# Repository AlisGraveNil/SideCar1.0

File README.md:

# SideCar
 a macropad with nav and num clusters

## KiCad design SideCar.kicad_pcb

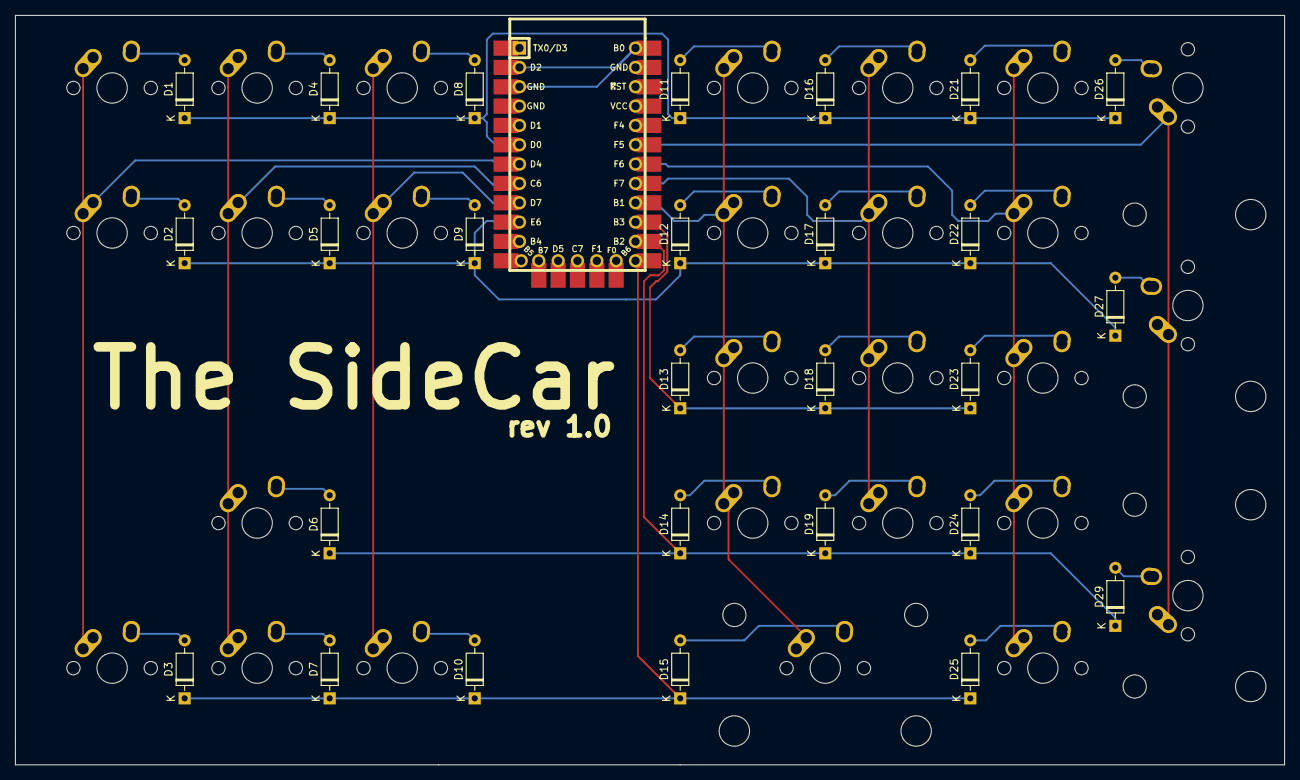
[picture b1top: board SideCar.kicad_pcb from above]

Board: 2 copper layers, 166.7 x 98.4 mm, 55 parts (0 on the bottom side), 40 nets.

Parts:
D1, D2, D3, D4, D5, D6, D7, D8, D9, D10, D11, D12, D13, D14, D15, D16, D17, D18, D19, D21, D22, D23, D24, D25, D26, D27, D29: D_Small; D_DO-35_SOD27_P7.62mm_Horizontal
MX1, MX2, MX3, MX4, MX5, MX6, MX7, MX8, MX9, MX10, MX11, MX12, MX13, MX14, MX16, MX17, MX18, MX19, MX21, MX22, MX23, MX24, MX25, MX26: MX-NoLED; MX-1U-NoLED
MX15, MX27, MX29: MX-NoLED; MX-2U-NoLED
U1: Elite-C; Elite-C-castellated-29pin-holes

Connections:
GND: U1.2, U1.3, U1.24
unnamed: D1.2, MX1.2
unnamed: D2.2, MX2.2
unnamed: D3.2, MX3.2
unnamed: D4.2, MX4.2
unnamed: D5.2, MX5.2
unnamed: D6.2, MX6.2
unnamed: D7.2, MX7.2
unnamed: D8.2, MX8.2
unnamed: D9.2, MX9.2
unnamed: D10.2, MX10.2
unnamed: D11.2, MX11.2
unnamed: D12.2, MX12.2
unnamed: D13.2, MX13.2
unnamed: D14.2, MX14.2
unnamed: D15.2, MX15.2
unnamed: D16.2, MX16.2
unnamed: D17.2, MX17.2
unnamed: D18.2, MX18.2
unnamed: D19.2, MX19.2
unnamed: D21.2, MX21.2
unnamed: D22.2, MX22.2
unnamed: D23.2, MX23.2
unnamed: D24.2, MX24.2
unnamed: D25.2, MX25.2
unnamed: D26.2, MX26.2
unnamed: D27.2, MX27.2
unnamed: D29.2, MX29.2
col0: MX1.1, MX2.1, MX3.1, U1.7
col1: MX4.1, MX5.1, MX6.1, MX7.1, U1.8
col2: MX8.1, MX9.1, MX10.1, U1.9
col3: MX11.1, MX12.1, MX13.1, MX14.1, MX15.1, U1.16
col4: MX16.1, MX17.1, MX18.1, MX19.1, U1.17
col5: MX21.1, MX22.1, MX23.1, MX24.1, MX25.1, U1.18
col6: MX26.1, MX27.1, MX29.1, U1.19
row0: D1.1, D4.1, D8.1, D11.1, D16.1, D21.1, D26.1, U1.6
row1: D2.1, D5.1, D9.1, D12.1, D17.1, D22.1, D27.1, U1.10
row2: D13.1, D18.1, D23.1, U1.15
row3: D6.1, D14.1, D19.1, D24.1, D29.1, U1.14
row4: D3.1, D7.1, D10.1, D15.1, D25.1, U1.13

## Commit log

2020-05-04 5/3/20 v3
2020-05-04 5/4/20 v1
